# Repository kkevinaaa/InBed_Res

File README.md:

## 设备设计

### 1.1 目标

本项目制作一个小型立方体番茄钟。设备顶面放置小尺寸单色 OLED 屏幕，用于显示当前时间、倒计时、电量和状态。与顶面相邻的四个侧面均可作为接触桌面的“底面”，用户通过翻滚立方体 90° 启动或切换计时状态。

设备不设置实体按钮，主要依赖姿态变化和摇晃动作交互。外壳面向 3D 打印设计，预留 Type-C 充电口，内部结构便于拆卸、调试和后续缩小体积。

### 1.2 交互与功能

设备默认处于时钟状态，屏幕显示当前时间和电量。长时间无操作后，OLED 熄灭，设备进入低功耗状态。轻微晃动或姿态变化会重新点亮屏幕。

立方体翻滚到指定侧面并稳定放置后，开始一次番茄钟计时，默认 25 分钟。计时过程中，屏幕显示剩余时间。计时结束后，蜂鸣器提醒，并显示结束状态，随后返回时钟状态。

计时过程中检测到暂停姿态，即屏幕面朝上时，设备暂停当前计时，屏幕面重新转向侧面时恢复计时。

计时过程中检测到取消姿态时，设备停止当前计时，短暂显示暂停提示后回到时钟状态。

快速摇晃用于进入 BLE 设置模式。一般情况下 BLE 关闭，只有快速摇晃触发后短时间开启。手机连接后设置当前时间、默认番茄钟时长、蜂鸣提醒方式、屏幕熄灭时间等参数。设置完成或连接超时后关闭 BLE。

```mermaid
stateDiagram-v2
    [*] --> IdleClock

    IdleClock: 时钟显示
    ScreenOff: 熄屏低功耗
    PomodoroRunning: 番茄钟计时
    PomodoroPaused: 暂停提示
    Alarm: 结束提醒
    BLESetting: BLE 设置模式

    IdleClock --> ScreenOff: 无操作超时
    ScreenOff --> IdleClock: 轻微晃动 / 姿态变化

    IdleClock --> PomodoroRunning: 翻滚到计时面并稳定放置
    PomodoroRunning --> Alarm: 倒计时结束
    Alarm --> IdleClock: 蜂鸣提醒结束

    PomodoroRunning --> PomodoroPaused: 翻滚到暂停/取消姿态
    PomodoroPaused --> IdleClock: 暂停提示结束

    IdleClock --> BLESetting: 快速摇晃
    ScreenOff --> BLESetting: 快速摇晃
    BLESetting --> IdleClock: 设置完成 / 连接超时
```

### 1.3 硬件方案

主控使用 ESP32-C3，开发环境为 PlatformIO + Arduino framework。ESP32-C3 负责读取传感器、驱动屏幕、控制蜂鸣器，并通过 BLE 与手机通信。

屏幕使用 SSD1327 单色 OLED。OLED 采用黑底白字显示，没有 TFT 背光常亮问题，适合电池供电设备。第一版只要求清晰显示时间、电量、倒计时和状态提示。

姿态检测使用 SC7A20H 三轴加速度传感器，通过 I2C 与 ESP32-C3 通信。第一阶段使用轮询读取三轴数据，调试六面识别、稳定放置判断、轻微晃动唤醒和快速摇晃检测。后续使用 INT 引脚做低功耗运动中断唤醒。

提醒部分使用 12085 蜂鸣器，阻抗约 16Ω。蜂鸣器通过 MOSFET 或三极管由 GPIO 控制。若使用无源蜂鸣器，ESP32-C3 输出 PWM；若使用有源蜂鸣器，GPIO 只控制开关。

电池使用小型单节聚合物锂电池。充电接口为 Type-C，充电电路使用单节锂电充电保护方案。系统电源可先采用电池升压到 5V 后接 ESP32-C3 开发板，也可后续改为电池经 3.3V 稳压/升降压后直接供电。电量检测第一版使用电阻分压接 ADC，后续可改用 MAX17048 电量计。

### 1.4 低功耗策略

静息状态下关闭 OLED，ESP32-C3 进入低功耗模式，BLE 默认关闭，SC7A20H 保持低功耗运动检测。检测到运动后唤醒主控，再读取完整三轴数据并判断动作类型。

低功耗逻辑的核心是：屏幕不常亮，BLE 不常开，ESP32-C3 不长期高频轮询。第一版先验证功能，后续再优化中断唤醒和静态电流。

### 1.5 第一版范围

第一版验证核心功能，不追求极致小体积和最终外观。目标包括：OLED 显示时间、电量和倒计时；SC7A20H 识别六个方向；翻滚启动 25 分钟计时；翻滚暂停；计时结束蜂鸣提醒；快速摇晃进入 BLE 设置；BLE 设置基础参数；无操作熄屏；晃动唤醒。

第一版外壳先使用较大的 3D 打印结构，优先保证安装、拆卸、测量和调试方便。功能稳定后再优化内部布局、屏幕开窗、接口位置和整体尺寸。

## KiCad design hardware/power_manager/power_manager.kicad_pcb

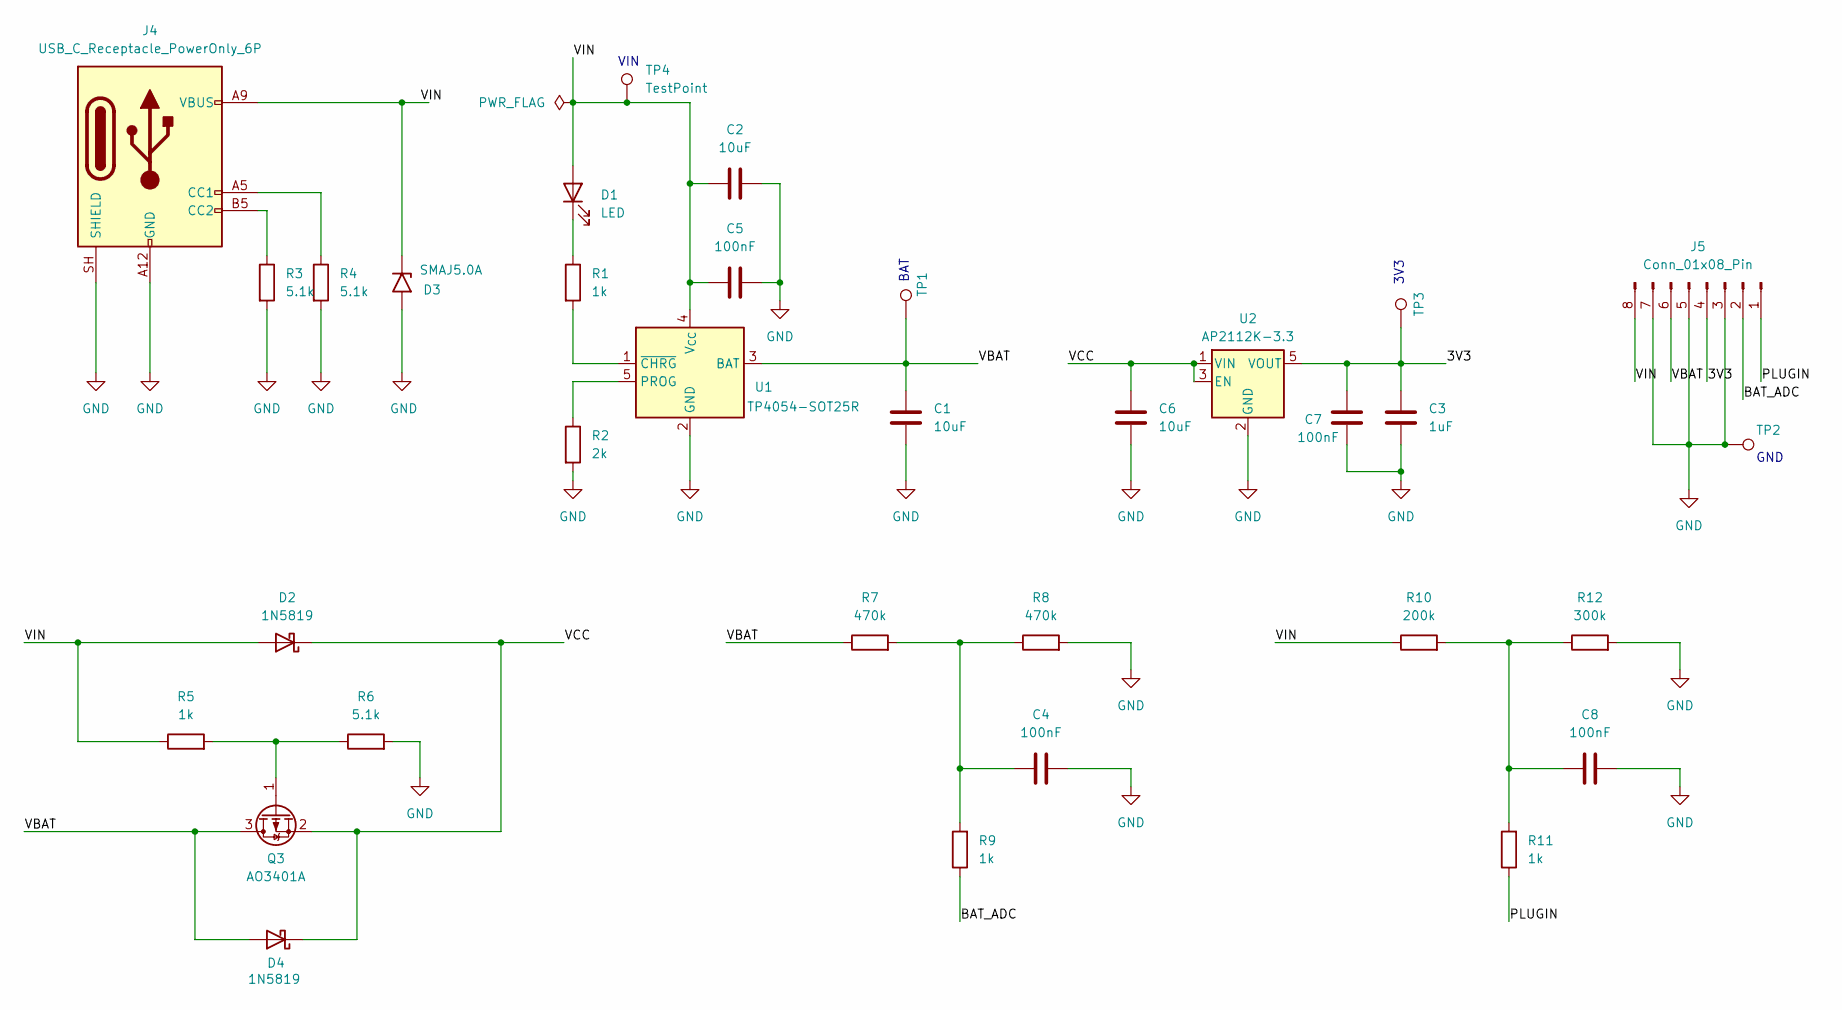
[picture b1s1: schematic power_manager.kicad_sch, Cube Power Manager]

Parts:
C1, C2, C6: 10uF; C_0805_2012Metric
C3: 1uF; C_0805_2012Metric
C4, C5, C7, C8: 100nF; C_0805_2012Metric
D1: LED; LED_D3.0mm
D2, D4: 1N5819; D_DO-41_SOD81_P10.16mm_Horizontal
D3: SMAJ5.0A; D_SMA
J4: USB_C_Receptacle_PowerOnly_6P; USB_C_Receptacle_GCT_USB4125-xx-x_6P_TopMnt_Horizontal
J5: Conn_01x08_Pin; PinHeader_1x08_P2.54mm_Vertical
Q3: AO3401A; SOT-23
R1, R5, R9, R11: 1k; R_Axial_DIN0207_L6.3mm_D2.5mm_P10.16mm_Horizontal
R2: 2k; R_Axial_DIN0207_L6.3mm_D2.5mm_P10.16mm_Horizontal
R3, R4, R6: 5.1k; R_Axial_DIN0207_L6.3mm_D2.5mm_P10.16mm_Horizontal
R7, R8: 470k; R_Axial_DIN0207_L6.3mm_D2.5mm_P10.16mm_Horizontal
R10: 200k; R_Axial_DIN0207_L6.3mm_D2.5mm_P10.16mm_Horizontal
R12: 300k; R_Axial_DIN0207_L6.3mm_D2.5mm_P10.16mm_Horizontal
TP1, TP2, TP3: TestPoint_Pad_D1.5mm
TP4: TestPoint; TestPoint_Pad_D1.5mm
U1: TP4054-SOT25R; TSOT-23-5
U2: AP2112K-3.3; SOT-23-5

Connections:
/3V3: C3.1, C7.2, J5.4, TP3.1 (1_1), U2.5 (VOUT)
/BAT_ADC: J5.2, R9.1
/PLUGIN: J5.1, R11.1
/VBAT: C1.1, D4.2 (A), J5.6, Q3.3 (D), R7.1, TP1.1 (1_1), U1.3 (BAT)
/VCC: C6.1, D2.1 (K), D4.1 (K), Q3.2 (S), U2.1 (VIN), U2.3 (EN)
/VIN: C2.1, C5.1, D1.2 (A), D2.2 (A), D3.1 (A1), J4.A9 (VBUS), J4.B9 (VBUS), J5.8, R5.1, R10.1, TP4.1 (1_1), U1.4 (V_{CC})
GND: C1.2, C2.2, C3.2, C4.2, C5.2, C6.2, C7.1, C8.2, D3.2 (A2), J4.A12 (GND), J4.B12 (GND), J4.SH (SHIELD), J5.3, J5.5, J5.7, R2.2, R3.2, R4.2, R6.2, R8.2, R12.2, TP2.1 (1_1), U1.2 (GND), U2.2 (GND)
unnamed: C4.1, R7.2, R8.1, R9.2
unnamed: C8.1, R10.2, R11.2, R12.1
unnamed: D1.1 (K), R1.1
unnamed: J4.A5 (CC1), R4.1
unnamed: J4.B5 (CC2), R3.1
unnamed: Q3.1 (G), R5.2, R6.1
unnamed: R2.1, U1.5 (PROG)
unnamed: R1.2, U1.1 (~CHRG)

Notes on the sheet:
3V3
BAT
VIN
GND

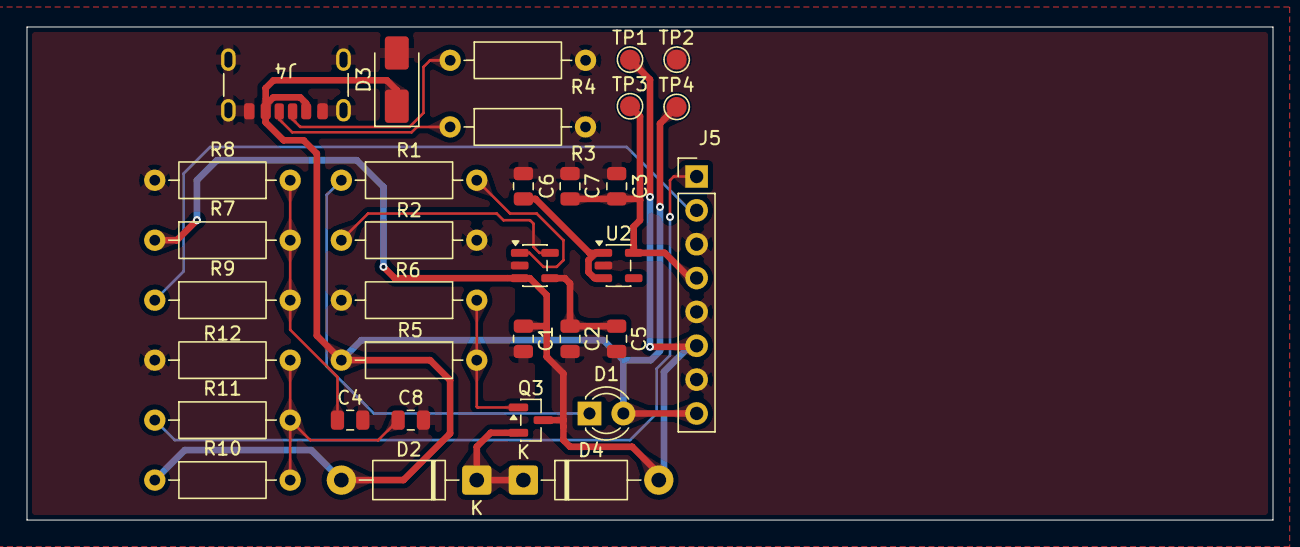
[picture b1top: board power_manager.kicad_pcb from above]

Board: 2 copper layers, 93.5 x 37.0 mm, 33 parts (0 on the bottom side), 15 nets.

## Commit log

2026-06-26 Initialize
2026-06-26 Add:Layout, Readme, references
2026-06-26 Imp: Readme
2026-06-26 Fix: Readme
2026-06-27 Imp: Powermanager
2026-06-28 Imp: powermanager schematic v0.2
2026-06-29 Add: PCB
2026-06-29 Imp: PCB FInish
2026-06-29 Fix: Add 3D Pics
2026-06-29 Add: Power_Supply.md
